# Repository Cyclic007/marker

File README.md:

This is a RP2040 dev-bord that has wireless capabilities 

It uses a  DWM1001 for wireless and has a USB-C port for interface

I can't get the PCB made any closer and I need to use JLC PCB

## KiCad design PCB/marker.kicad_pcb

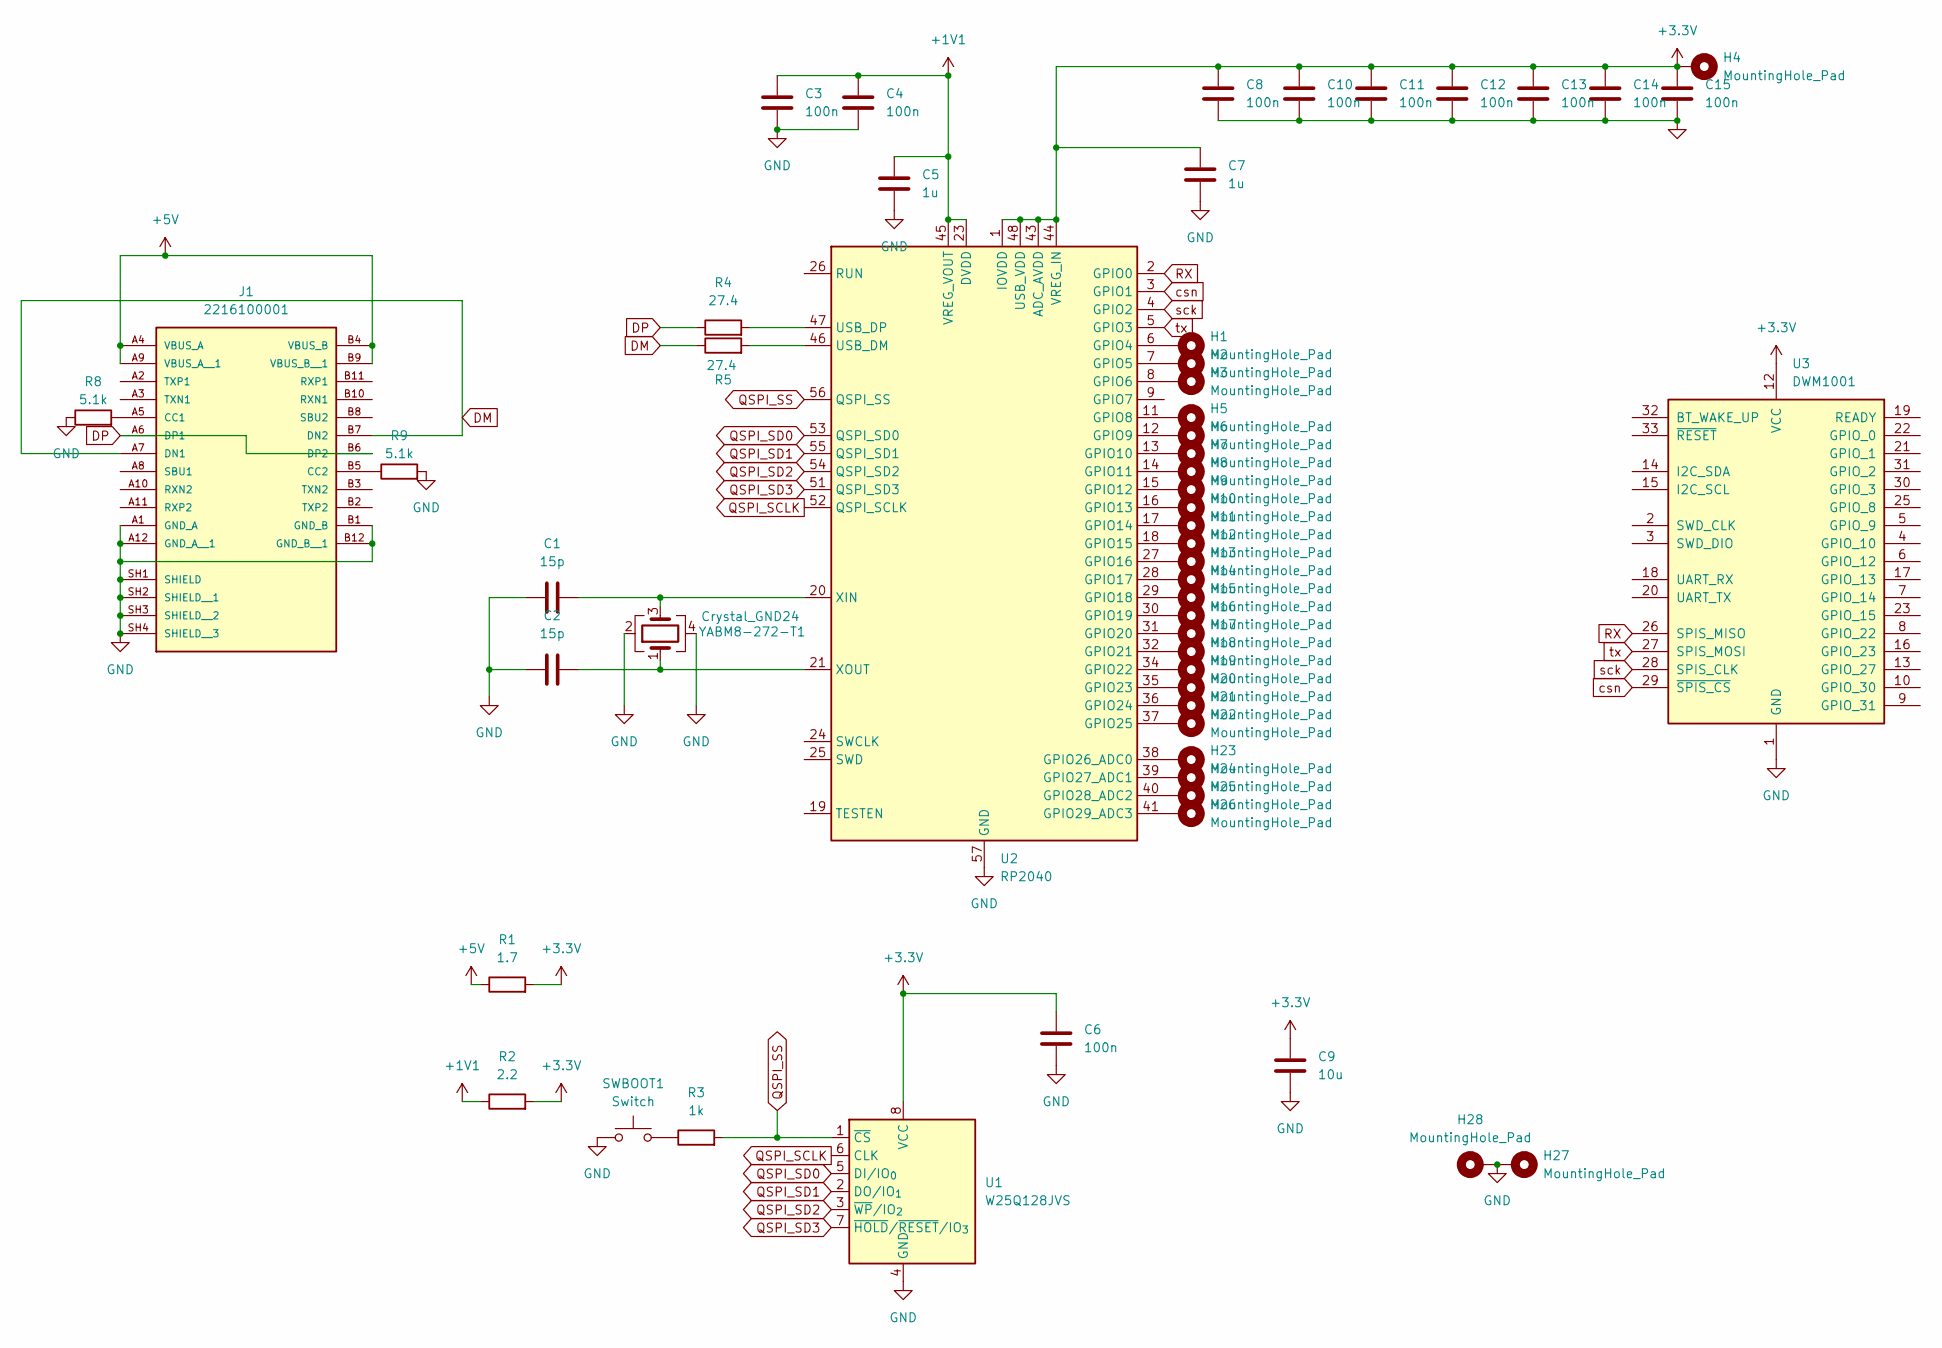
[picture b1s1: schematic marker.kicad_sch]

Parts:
C1, C2: 15p; C_0402_1005Metric
C3, C4, C6, C8, C10, C11, C12, C13, C14, C15: 100n; C_0402_1005Metric
C5, C7: 1u; C_0402_1005Metric
C9: 10u; C_0402_1005Metric
H1, H2, H3, H4, H5, H6, H7, H8, H9, H10, H11, H12, H13, H14, H15, H16, H17, H18, H19, H20, H21, H22, H23, H24, H25, H26, H27, H28: MountingHole_Pad; MountingHole_2.5mm_Pad_Via
J1: 2216100001; MOLEX_2216100001; PARTREV A
R1: 1.7; R_0402_1005Metric
R2: 2.2; R_0402_1005Metric
R3: 1k; R_0402_1005Metric
R4, R5: 27.4; R_0402_1005Metric
R8, R9: 5.1k; R_0402_1005Metric
SWBOOT1: Switch; SW_Push_1P1T_NO_CK_KSC6xxG
U1: W25Q128JVS; SOIC-8_5.3x5.3mm_P1.27mm
U2: RP2040; QFN-56-1EP_7x7mm_P0.4mm_EP3.2x3.2mm
U3: DWM1001; DecaWave_DWM1001
YABM8-272-T1: Crystal_GND24; XTAL_ABM8-272-T3

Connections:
+1V1: C3.1, C4.1, C5.1, R2.1, U2.23 (DVDD), U2.45 (VREG_VOUT), U2.50 (DVDD)
+3.3V: C6.1, C7.1, C8.1, C9.1, C10.1, C11.1, C12.1, C13.1, C14.1, C15.1, H4.1, R1.2, R2.2, U1.8 (VCC), U2.1 (IOVDD), U2.10 (IOVDD), U2.22 (IOVDD), U2.33 (IOVDD), U2.42 (IOVDD), U2.43 (ADC_AVDD), U2.44 (VREG_IN), U2.48 (USB_VDD), U2.49 (IOVDD), U3.12 (VCC)
+5V: J1.A4 (VBUS_A), J1.A9 (VBUS_A__1), J1.B4 (VBUS_B), J1.B9 (VBUS_B__1), R1.1
DM: J1.A7 (DN1), J1.B7 (DN2), R5.1
DP: J1.A6 (DP1), J1.B6 (DP2), R4.1
GND: C1.1, C2.1, C3.2, C4.2, C5.2, C6.2, C7.2, C8.2, C9.2, C10.2, C11.2, C12.2, C13.2, C14.2, C15.2, H27.1, H28.1, J1.A1 (GND_A), J1.A12 (GND_A__1), J1.B1 (GND_B), J1.B12 (GND_B__1), J1.SH1 (SHIELD), J1.SH2 (SHIELD__1), J1.SH3 (SHIELD__2), J1.SH4 (SHIELD__3), R8.1, R9.2, SWBOOT1.1, U1.4 (GND), U2.57 (GND), U3.1 (GND), U3.11 (GND), U3.24 (GND), U3.34 (GND), YABM8-272-T1.2, YABM8-272-T1.4
unnamed: J1.A5 (CC1), R8.2
unnamed: J1.B5 (CC2), R9.1
unnamed: R3.1, SWBOOT1.2
unnamed: H1.1, U2.6 (GPIO4)
unnamed: H2.1, U2.7 (GPIO5)
unnamed: H3.1, U2.8 (GPIO6)
unnamed: H5.1, U2.11 (GPIO8)
unnamed: H6.1, U2.12 (GPIO9)
unnamed: H7.1, U2.13 (GPIO10)
unnamed: H8.1, U2.14 (GPIO11)
unnamed: H9.1, U2.15 (GPIO12)
unnamed: H10.1, U2.16 (GPIO13)
unnamed: H11.1, U2.17 (GPIO14)
unnamed: H12.1, U2.18 (GPIO15)
unnamed: H13.1, U2.27 (GPIO16)
unnamed: H14.1, U2.28 (GPIO17)
unnamed: H15.1, U2.29 (GPIO18)
unnamed: H16.1, U2.30 (GPIO19)
unnamed: H17.1, U2.31 (GPIO20)
unnamed: H18.1, U2.32 (GPIO21)
unnamed: H19.1, U2.34 (GPIO22)
unnamed: H20.1, U2.35 (GPIO23)
unnamed: H21.1, U2.36 (GPIO24)
unnamed: H22.1, U2.37 (GPIO25)
unnamed: H23.1, U2.38 (GPIO26_ADC0)
unnamed: H24.1, U2.39 (GPIO27_ADC1)
unnamed: H25.1, U2.40 (GPIO28_ADC2)
unnamed: H26.1, U2.41 (GPIO29_ADC3)
unnamed: R5.2, U2.46 (USB_DM)
unnamed: R4.2, U2.47 (USB_DP)
unnamed: C1.2, U2.20 (XIN), YABM8-272-T1.3
unnamed: C2.2, U2.21 (XOUT), YABM8-272-T1.1
QSPI_SCLK: U1.6 (CLK), U2.52 (QSPI_SCLK)
QSPI_SD0: U1.5 (DI/IO_{0}), U2.53 (QSPI_SD0)
QSPI_SD1: U1.2 (DO/IO_{1}), U2.55 (QSPI_SD1)
QSPI_SD2: U1.3 (~WP/IO_{2}), U2.54 (QSPI_SD2)
QSPI_SD3: U1.7 (~HOLD/~RESET/IO_{3}), U2.51 (QSPI_SD3)
QSPI_SS: R3.2, U1.1 (~CS), U2.56 (QSPI_SS)
RX: U2.2 (GPIO0), U3.26 (SPIS_MISO)
csn: U2.3 (GPIO1), U3.29 (~SPIS_CS)
sck: U2.4 (GPIO2), U3.28 (SPIS_CLK)
tx: U2.5 (GPIO3), U3.27 (SPIS_MOSI)

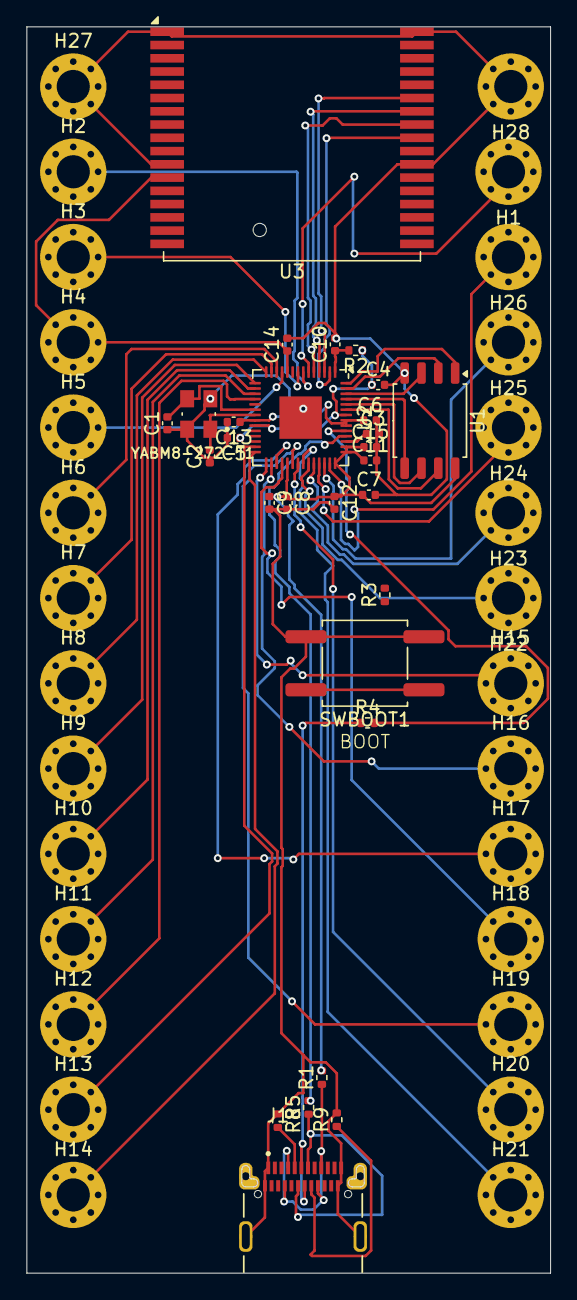
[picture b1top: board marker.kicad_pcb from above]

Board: 2 copper layers, 39.5 x 94.0 mm, 56 parts (0 on the bottom side), 48 nets.

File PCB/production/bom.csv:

Designator,Footprint,Quantity,Value,LCSC Part #
"C1, C2",0402,2,15p,
"C10, C11, C12, C13, C14, C15, C3, C4, C6, C8",0402,10,100n,
"C5, C7",0402,2,1u,
C9,0402,1,10u,
J1,MOLEX_2216100001,1,2216100001,
R1,0402,1,1.7,
R2,0402,1,2.2,
R3,0402,1,1k,
"R4, R5",0402,2,27.4,
"R8, R9",0402,2,5.1k,
SWBOOT1,SW_Push_1P1T_NO_CK_KSC6xxG,1,Switch,
U1,SOIC-8_5.3x5.3mm_P1.27mm,1,W25Q128JVS,
U2,QFN-56-1EP_7x7mm_P0.4mm_EP3.2x3.2mm,1,RP2040,
U3,DecaWave_DWM1001,1,DWM1001,
YABM8-272-T1,XTAL_ABM8-272-T3,1,Crystal_GND24,

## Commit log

2025-11-18 fixing things
2025-11-18 adding thing
2025-11-18 Wasteing time
2025-11-19 doing the things
2025-11-19 fab stuff
2025-11-19 the boring stuff
